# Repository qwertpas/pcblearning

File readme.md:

# pcblearning
A collection of PCB and firmware projects for learning PCB design. Projects are designed to have few components, cheap, yet rich in potential features.

## Using common libraries
1. After creating a new project in KiCad, copy the contents of `copy-into-your-project` into the same folder that contains your project's `.kicad_pcb` file.
2. Restart KiCad. When you place new components in the schematic or PCB editor, the `pcblearning` library should be available.

## minrc1
Tiny wheeled robot with two PM08 stepper motors, three microphones, and a buzzer. ESP32S3 supermini dev board allows for wireless control, USB-C battery charging, and running small neural networks. Microphones and buzzer may be useful for locating other robots, echolocation, and detecting surface properties (through vibration/noise from ground contact).

## minrc-ref
Even more minimal than minrc1: just an ESP32S3-supermini, 4x DRV8837 motor drivers, 2x stepper motors, and resistor divider voltage sense. Intended as a reference design to be used as a starting point.

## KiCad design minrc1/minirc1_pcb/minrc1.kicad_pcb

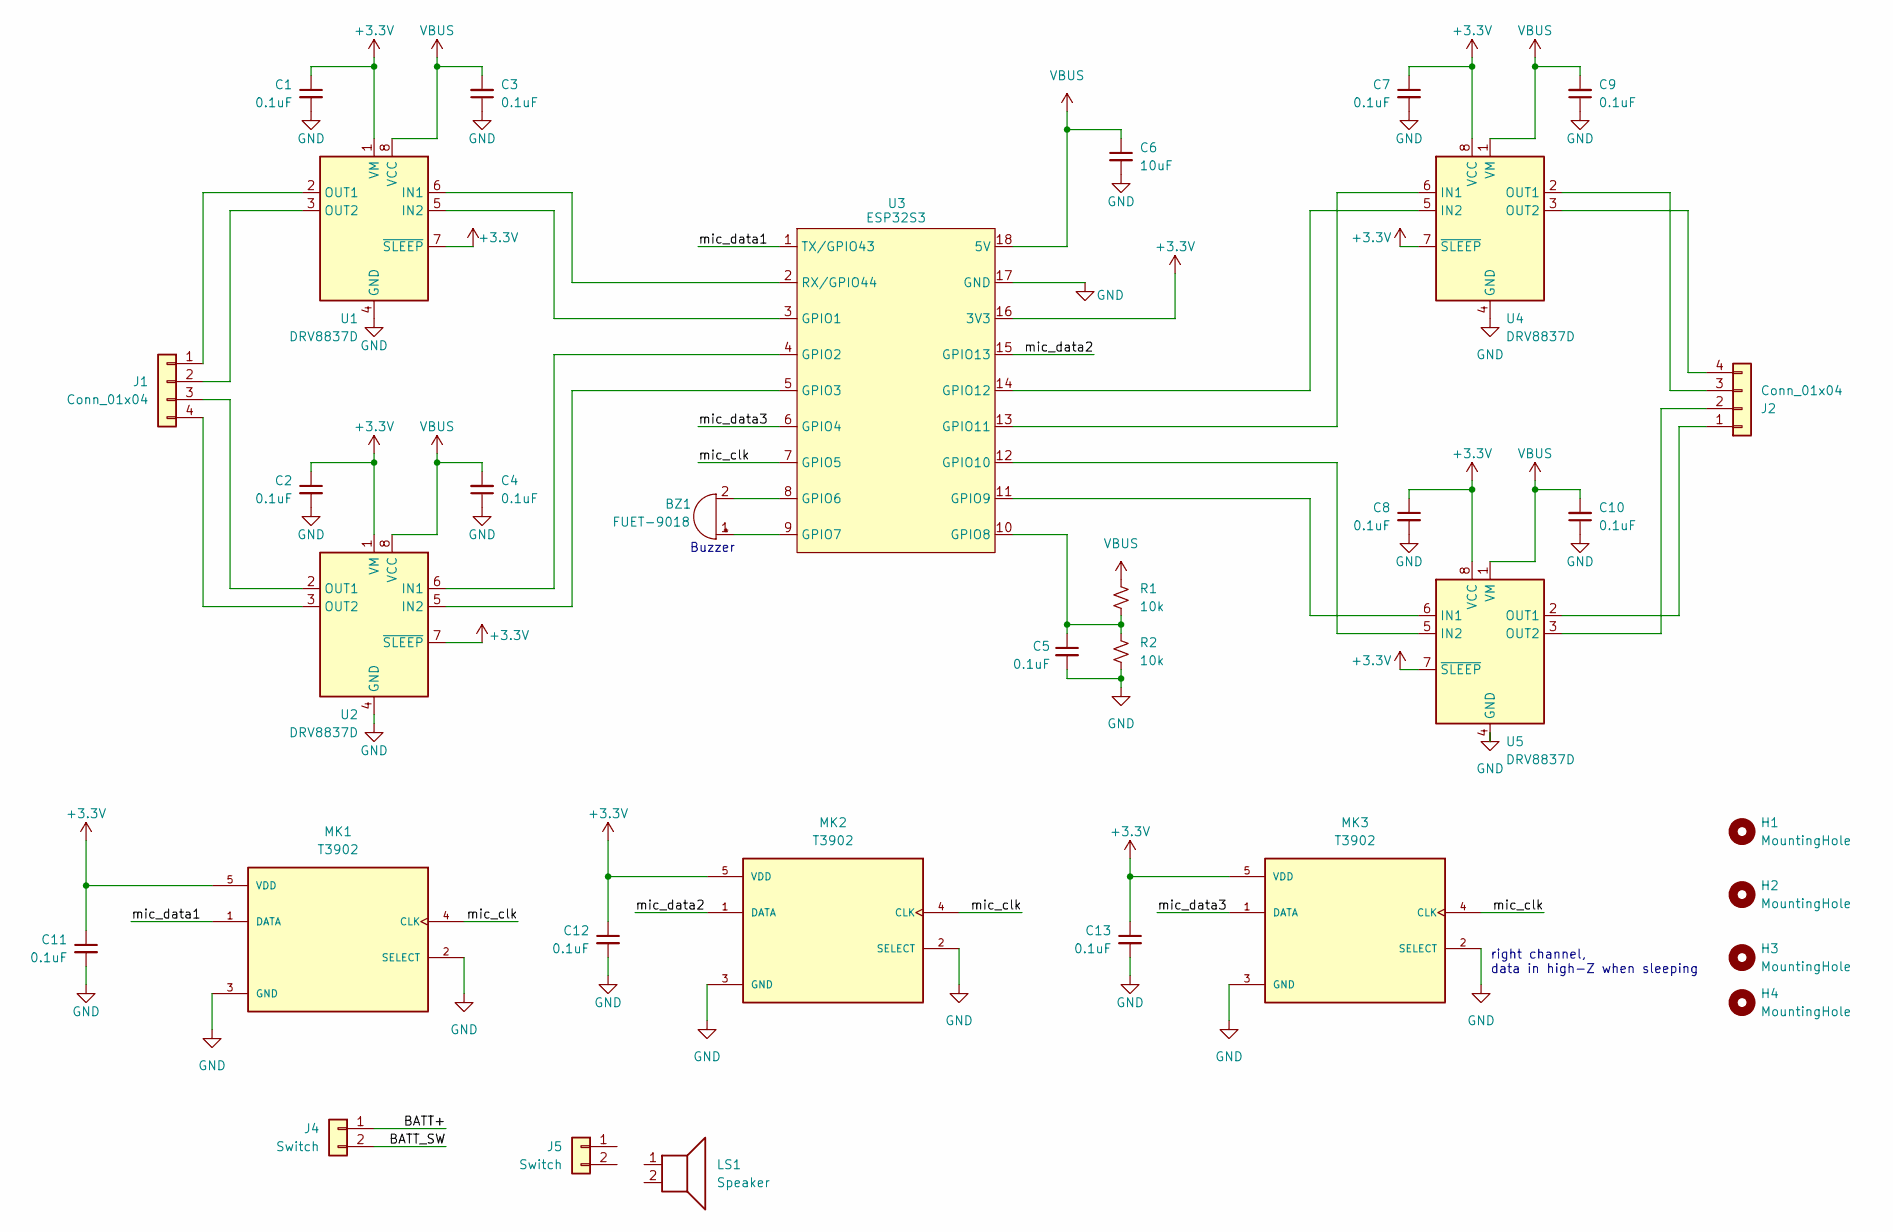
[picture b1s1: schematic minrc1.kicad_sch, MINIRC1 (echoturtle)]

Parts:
BZ1: FUET-9018; Buzzer_CUI_CPT-9019S-SMT
C1, C2, C3, C4, C5, C7, C8, C9, C10, C11, C12, C13: 0.1uF; C_0402_1005Metric
C6: 10uF; C_0402_1005Metric
H1, H2, H3, H4: MountingHole; MountingHole_2.2mm_M2
J1, J2: Conn_01x04; microstepper
J4, J5: Switch; PinHeader_1x02_P2.54mm_Vertical
LS1: Speaker; Speaker_CUI_CMR-1206S-67
MK1, MK2, MK3: T3902; MIC_T3902; PARTREV 1.0
R1, R2: 10k; R_0402_1005Metric
U1, U2, U4, U5: DRV8837D; WSON-8-1EP_2x2mm_P0.5mm_EP0.9x1.6mm; LCSC C39159
U3: ESP32S3; esp32s3-supermini

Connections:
+3.3V: C1.1, C2.1, C7.1, C8.1, C11.1, C12.1, C13.1, MK1.5 (VDD), MK2.5 (VDD), MK3.5 (VDD), U1.1 (VM), U1.7 (~SLEEP), U2.1 (VM), U2.7 (~SLEEP), U3.16 (3V3), U4.7 (~SLEEP), U4.8 (VCC), U5.7 (~SLEEP), U5.8 (VCC)
/BATT+: J4.1
/BATT_SW: J4.2
/mic_clk: MK1.4 (CLK), MK2.4 (CLK), MK3.4 (CLK), U3.7 (GPIO5)
/mic_data1: MK1.1 (DATA), U3.1 (TX/GPIO43)
/mic_data2: MK2.1 (DATA), U3.15 (GPIO13)
/mic_data3: MK3.1 (DATA), U3.6 (GPIO4)
GND: C1.2, C2.2, C3.1, C4.1, C5.2, C6.2, C7.2, C8.2, C9.1, C10.1, C11.2, C12.2, C13.2, MK1.2 (SELECT), MK1.3 (GND), MK2.2 (SELECT), MK2.3 (GND), MK3.2 (SELECT), MK3.3 (GND), R2.2, U1.4 (GND), U1.9 (GND), U2.4 (GND), U2.9 (GND), U3.17 (GND), U4.4 (GND), U4.9 (GND), U5.4 (GND), U5.9 (GND)
unnamed: BZ1.1 (+), U3.9 (GPIO7)
unnamed: BZ1.2 (-), U3.8 (GPIO6)
unnamed: J1.1, U1.2 (OUT1)
unnamed: J1.2, U1.3 (OUT2)
unnamed: J1.3, U2.2 (OUT1)
unnamed: J1.4, U2.3 (OUT2)
unnamed: J2.1, U5.2 (OUT1)
unnamed: J2.2, U5.3 (OUT2)
unnamed: J2.3, U4.2 (OUT1)
unnamed: J2.4, U4.3 (OUT2)
unnamed: U1.6 (IN1), U3.2 (RX/GPIO44)
unnamed: U1.5 (IN2), U3.3 (GPIO1)
unnamed: U2.6 (IN1), U3.4 (GPIO2)
unnamed: U2.5 (IN2), U3.5 (GPIO3)
unnamed: C5.1, R1.2, R2.1, U3.10 (GPIO8)
unnamed: U3.11 (GPIO9), U5.6 (IN1)
unnamed: U3.12 (GPIO10), U5.5 (IN2)
unnamed: U3.13 (GPIO11), U4.6 (IN1)
unnamed: U3.14 (GPIO12), U4.5 (IN2)
VBUS: C3.2, C4.2, C6.1, C9.2, C10.2, R1.1, U1.8 (VCC), U2.8 (VCC), U3.18 (5V), U4.1 (VM), U5.1 (VM)

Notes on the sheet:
right channel, data in high-Z when sleeping
Buzzer

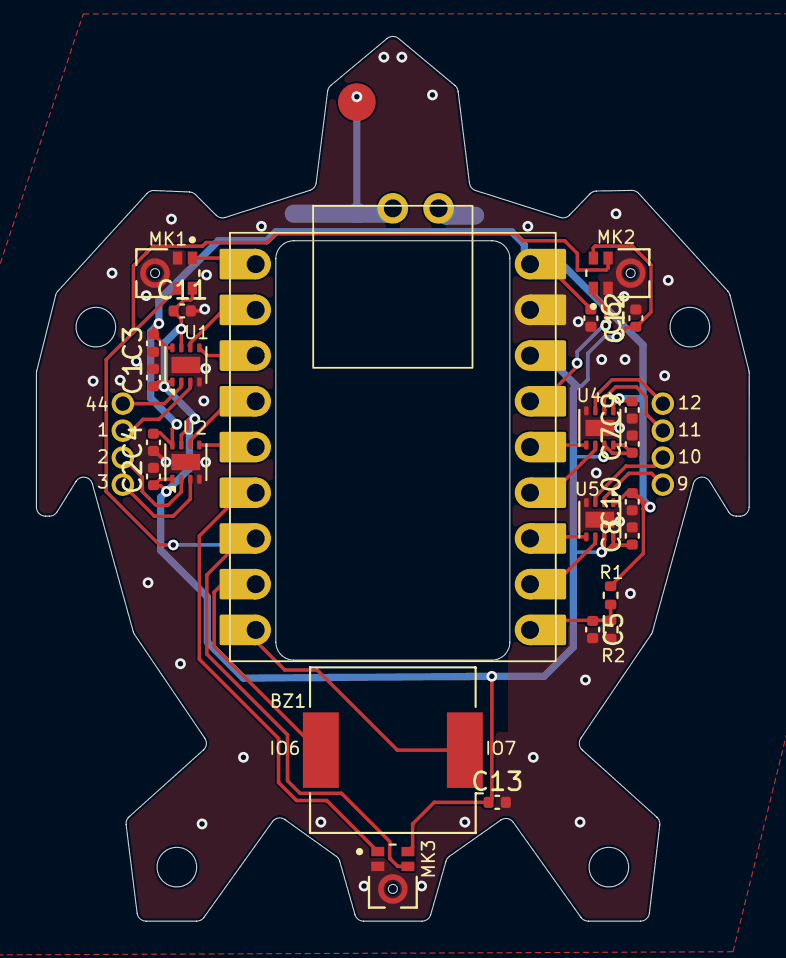
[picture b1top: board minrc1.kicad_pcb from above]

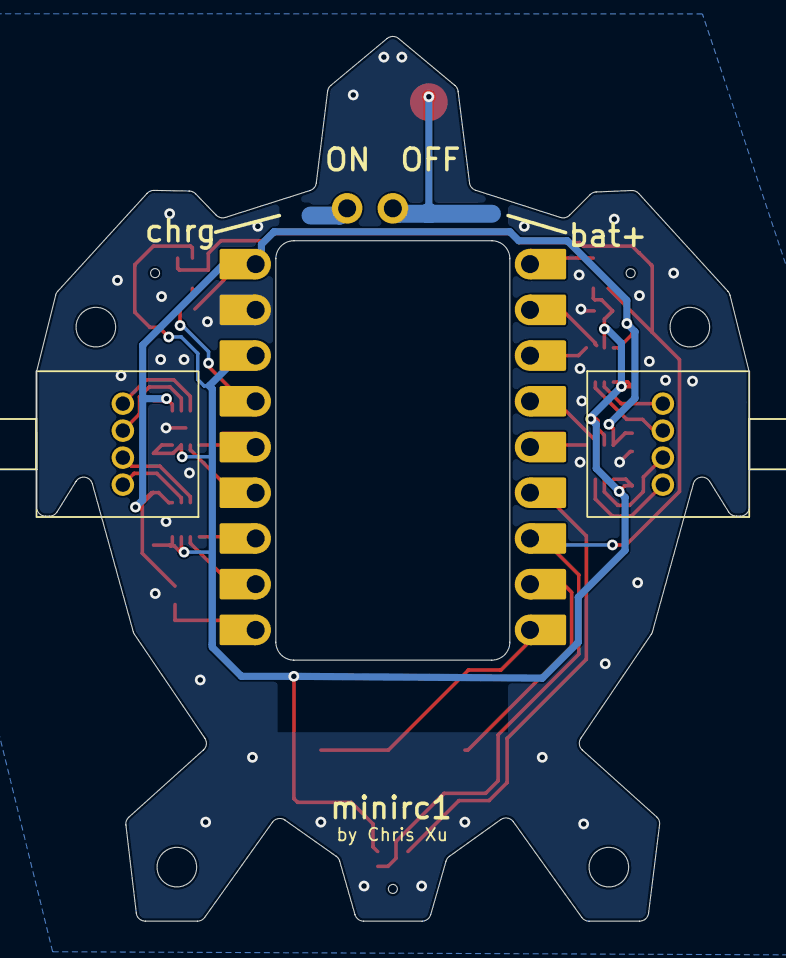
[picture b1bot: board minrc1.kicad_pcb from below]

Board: 2 copper layers, 39.6 x 49.1 mm, 31 parts (3 on the bottom side), 26 nets.

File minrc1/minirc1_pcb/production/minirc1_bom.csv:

Designator,Footprint,Quantity,Value,LCSC Part #
BZ1,Buzzer_CUI_CPT-9019S-SMT,1,FUET-9018,
"C1, C10, C11, C12, C13, C2, C3, C4, C5, C7, C8, C9",0402,12,0.1uF,
C6,0402,1,10uF,
"J1, J2",microstepper,2,Conn_01x04,
J4,PinHeader_1x02_P2.54mm_Vertical,1,Switch,
"MK1, MK2, MK3",MIC_T3902,3,T3902,
"R1, R2",0402,2,10k,
"U1, U2, U4, U5",WSON-8-1EP_2x2mm_P0.5mm_EP0.9x1.6mm,4,DRV8837D,C39159
U3,esp32s3-supermini,1,ESP32S3,

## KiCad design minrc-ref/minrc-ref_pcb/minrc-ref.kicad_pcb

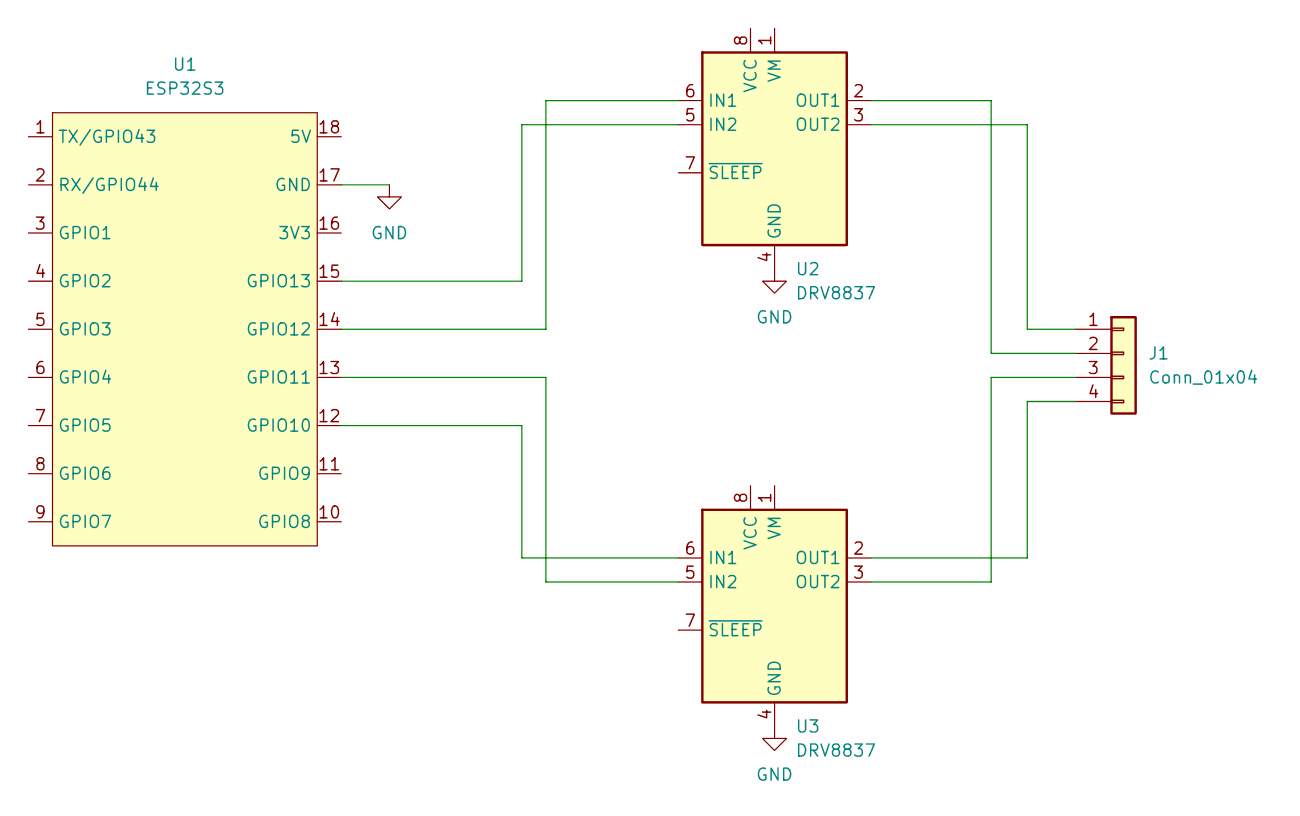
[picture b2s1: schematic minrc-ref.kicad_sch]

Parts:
J1: Conn_01x04; PM08_stepper_motor
U1: ESP32S3; ESP32-S3-SUPERMINI
U2, U3: DRV8837; WSON-8-1EP_2x2mm_P0.5mm_EP0.9x1.6mm

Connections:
GND: U1.17 (GND), U2.4 (GND), U2.9 (GND), U3.4 (GND), U3.9 (GND)
unnamed: J1.1, U2.3 (OUT2)
unnamed: J1.2, U2.2 (OUT1)
unnamed: J1.3, U3.3 (OUT2)
unnamed: J1.4, U3.2 (OUT1)
unnamed: U1.12 (GPIO10), U3.6 (IN1)
unnamed: U1.13 (GPIO11), U3.5 (IN2)
unnamed: U1.14 (GPIO12), U2.6 (IN1)
unnamed: U1.15 (GPIO13), U2.5 (IN2)

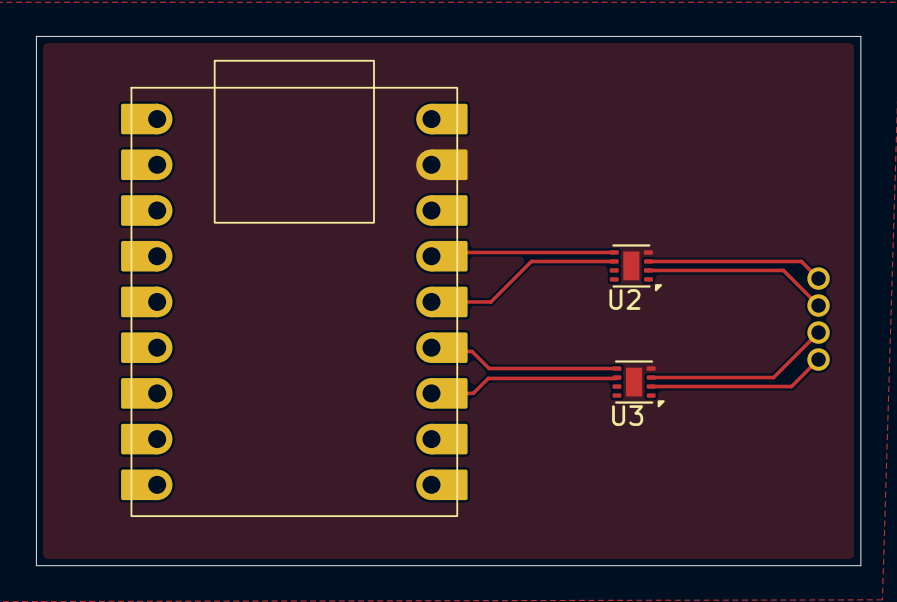
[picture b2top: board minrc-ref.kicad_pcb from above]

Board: 2 copper layers, 45.8 x 29.4 mm, 4 parts (1 on the bottom side), 9 nets.

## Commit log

2026-04-02 fix readme header
2026-04-03 ble stepper control, persist setings
2026-04-06 finish turtlebot
2026-04-06 add schematic image
2026-04-10 test common library
2026-04-10 workshop
2026-05-31 stepper gui and audio
